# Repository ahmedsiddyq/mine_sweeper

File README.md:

# Mine Sweeper

A software implementation of the classic Minesweeper game.

## Features
- Mine-field generation
- Cell revealing and flagging
- Game-state handling
- Win/loss detection

## Purpose
A practical programming project focused on algorithms, game logic, data structures, and user interaction.

## Author
**Ahmed Siddyq**

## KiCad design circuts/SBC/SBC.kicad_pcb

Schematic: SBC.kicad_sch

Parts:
C1, C5, C10, C13, C14, C15, C16, C46, C51, C52, C53, C55, C56, C58, C63, C64, C65, C80, C95: 2uf; C_0805_2012Metric_Pad1.18x1.45mm_HandSolder
C2, C4, C11, C18, C22, C26, C36, C41, C42, C43, C44, C45, C47, C78, C87: 1nf; C_0201_0603Metric_Pad0.64x0.40mm_HandSolder
C3, C7, C9, C17, C48, C49, C50, C66, C67, C68, C69, C70, C71, C72, C79, C90, C98, C101, C104, C105: 100nf; C_0805_2012Metric_Pad1.18x1.45mm_HandSolder
C6, C19, C23, C27, C37, C54, C57, C60, C88, C96, C97: 470uf; CP_Radial_D8.0mm_P5.00mm
C8: 2pf; C_0805_2012Metric_Pad1.18x1.45mm_HandSolder
C12, C91: 33uf; CP_Radial_D4.0mm_P1.50mm
C20, C21, C28, C29, C34, C38, C39, C40, C82, C89, C99, C100, C102, C103: 2uf; R_0805_2012Metric_Pad1.20x1.40mm_HandSolder
C24, C25, C30, C31, C32, C33, C35, C73, C74, C83, C84, C85, C86, C92, C93: 100nf; R_0805_2012Metric_Pad1.20x1.40mm_HandSolder
C75, C76, C77, C94: C; C_0805_2012Metric_Pad1.18x1.45mm_HandSolder
C81: 470uf; CP_Elec_4x4.5
D1, D4, D5, D10, D12, D13, D14, D43, D44: LED; D_MiniMELF
D2, D3, D6, D7, D46, D47, D48, D49, D54, D55, D56, D57, D58, D59, D60, D61, D62, D63, D64, D65, D66, D67, D68: 1N4004-T_NRND; D_0603_1608Metric_Pad1.05x0.95mm_HandSolder; MPN 1N4004-T; Digi-Key_PN 1N4004DICT-ND
D8, D15, D16, D17, D18, D19: SMAJ6.5A; D_MiniMELF
D11, D21, D24: BZV55B3V3; D_MiniMELF
D20, D25, D26, D45: 1N4004-T_NRND; D_MiniMELF; MPN 1N4004-T; Digi-Key_PN 1N4004DICT-ND
D29, D30, D31, D32, D37, D38, D39, D40, D41, D42: 1N5822; D_MiniMELF
D33, D34, D35, D36: SMAJ26A; D_MiniMELF
D50, D52: L_LED; D_MiniMELF
D51, D53: R_LED; D_MiniMELF
F3, F4: 1A; D_SOD-128
F5, F7: 1A; C_0805_2012Metric_Pad1.18x1.45mm_HandSolder
IC1: PIC16F15243-I_SS; SSOP20_SS_MCH-M; Mouser Part Number 579-PIC16F15243-I/SS
J1: 640456-3; TE_640456-3; MPN 640456-3; Digi-Key_PN A19470-ND
J2: B5B-XH-A_LF__SN_; JST_B5B-XH-A_LF__SN_; MPN B5B-XH-A(LF)(SN); Digi-Key_PN 455-2270-ND
J3: Power; TE_282837-2
J4, J8, J10: DE9_Plug; DB9
J5, J7: OSTTC060162; CONN_6P-OSTTC_OST; MPN OSTTC060162; Digi-Key_PN ED2604-ND
J6: XT60-M; AMASS_XT60-M; PARTREV V1.2
J9: Conn_02x04_Odd_Even; PinHeader_2x04_P2.54mm_Vertical
J11: buzzer; TE_282837-2
J13: Conn_01x04_Pin; PinSocket_1x04_P2.54mm_Vertical
J14: 5v Power; TE_282837-2
J15: Barrel_Jack_MountingPin; BarrelJack_GCT_DCJ200-10-A_Horizontal
Q1, Q2, Q3, Q5, Q6, Q7: MMBTA06; SOT-23
Q4, Q8: IRFS4227; TO-263-3_TabPin2
Q10: BC817; SOT-23
Q11: AO3400A; SOT-23_Handsoldering
R1, R9, R12, R15, R16, R17, R30, R38, R43, R47, R56: 2k; R_0805_2012Metric_Pad1.20x1.40mm_HandSolder
R2, R3, R11, R13, R34, R35, R76, R114, R117, R119: 220; R_0805_2012Metric_Pad1.20x1.40mm_HandSolder
R4, R28, R29, R32, R54, R55, R58: 56k; R_0805_2012Metric_Pad1.20x1.40mm_HandSolder
R5, R6, R14, R36, R37, R60, R61, R62, R63, R120: 5.1k; R_0805_2012Metric_Pad1.20x1.40mm_HandSolder
R7, R21, R50, R51: 470; R_0805_2012Metric_Pad1.20x1.40mm_HandSolder
R8, R24, R25, R39, R52, R53, R64, R65, R66, R67, R68, R69, R70, R71, R80, R90, R91, R92, R93, R94, R95, R96, R97, R98, R107, R121, R122, R123, R124, R125, R126, R127: 10k; R_0805_2012Metric_Pad1.20x1.40mm_HandSolder
R10, R22, R33, R89, R118: 2.2k; R_0805_2012Metric_Pad1.20x1.40mm_HandSolder
R18, R20, R48, R49: 0.3; R_2512_6332Metric_Pad1.40x3.35mm_HandSolder
R19, R23, R46, R77, R112: 330; R_0805_2012Metric_Pad1.20x1.40mm_HandSolder
R26: 26k; R_0805_2012Metric_Pad1.20x1.40mm_HandSolder
R27, R31, R57: 100k; R_0805_2012Metric_Pad1.20x1.40mm_HandSolder
R40, R88, R100, R106: 200; R_0805_2012Metric_Pad1.20x1.40mm_HandSolder
R41, R111, R115, R116: 1.5k; R_0805_2012Metric_Pad1.20x1.40mm_HandSolder
R42: 10; R_0805_2012Metric_Pad1.20x1.40mm_HandSolder
R59, R73: 5k; R_0805_2012Metric_Pad1.20x1.40mm_HandSolder
R72, R74, R75, R84, R85, R86, R87, R109, R110: 1k; R_0805_2012Metric_Pad1.20x1.40mm_HandSolder
R99, R102, R104, R105: 1ohm; R_0805_2012Metric_Pad1.20x1.40mm_HandSolder
R101, R113: 1ohm op*; R_0805_2012Metric_Pad1.20x1.40mm_HandSolder
RV1, RV2: R_Potentiometer; Potentiometer_Bourns_3214W_Vertical
SW1, SW2, SW3, SW4, SW5, SW7: SW_Push; SW_DIP_SPSTx01_Slide_6.7x4.1mm_W6.73mm_P2.54mm_LowProfile_J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
SW6: rst; SW_DIP_SPSTx01_Slide_6.7x4.1mm_W6.73mm_P2.54mm_LowProfile_J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
U1: UC3843; SOIC-8_3.9x4.9mm_P1.27mm
U2, U3, U7, U8: BTS7960B; DPAK127P1490X440-8N; PARTREV 1.1
U4, U9: LM358DT; SOIC-8_3.9x4.9mm_P1.27mm; MPN LM358DT; Digi-Key_PN 497-1591-1-ND
U5: AMS1117-3.3; SOT-223-3_TabPin2
U10: ESP32-DEVKIT-V1; MODULE_ESP32_DEVKIT_V1; PARTREV N/A
U11: PinHeader_1x08_P2.54mm_Vertical
U12, U13: L7805; TO-252-2
U14: L7809; TO-220-3_Vertical
ZD1, ZD8: 3.3v; D_MiniMELF
ZD2, ZD3, ZD4, ZD5, ZD6, ZD7, ZD10, ZD11, ZD12, ZD31, ZD35, ZD36: BZV55B4V7; D_MiniMELF
ZD9: 20v; D_MiniMELF
ZD13, ZD14, ZD15, ZD16, ZD17, ZD18, ZD19, ZD20, ZD21, ZD22, ZD23, ZD24, ZD25, ZD26, ZD27, ZD28, ZD29, ZD30, ZD33, ZD34: 3.3v; D_SOD-123

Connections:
3.3v: C24.1, C35.1, C36.1, C37.1, C38.2, C47.1, C50.1, C53.1, C68.1, D5.2 (A), D6.1 (K), IC1.1 (VDD), J4.4, J8.4, J9.2, J10.4, R64.1, R65.2, R67.1, R69.2, R70.2, R71.2, R76.2, R80.2, R101.1, R105.2, R107.2, R113.1, ZD5.1 (K)
5v block: F7.2, J14.1
5v+: C25.1, C26.1, C27.1, C29.2, C49.1, C52.1, C64.1, C67.1, C76.1, D15.1 (A1), D17.1 (A1), D44.2 (A), D45.2 (A), F4.2, F7.1, J4.3, J5.2, J7.2, J8.3, J10.3, R8.1, R39.1, R40.2, R77.2, R102.1, R104.2, R109.2, R110.2, RV1.3, RV2.3, U10.30 (VIN), ZD7.1 (K), ZD10.1 (K), ZD11.1 (K)
9v+: C82.2, C85.1, C87.1, C88.1, C89.2, D2.2 (A), D43.2 (A), R15.1, R47.1, R99.2, U4.8 (VCC+), U9.8 (VCC+), ZD6.1 (K)
SDA: IC1.9 (RC7)
A1: IC1.5 (RC5), R61.1, ZD20.1 (K)
A2: IC1.7 (RC3), R63.1, ZD22.1 (K)
B1: IC1.2 (RA5), R60.2, ZD19.1 (K)
B2: IC1.8 (RC6), R62.2, ZD21.1 (K)
CS: D3.1 (K), D7.1 (K), U1.3 (CS)
Current_limt1: C83.1, U9.5
Current_limt2: C7.1, R22.1, U4.5
Data_ready: U10.15 (D23), U11.8 (DRDY)
FRQ: D21.1 (K), J13.3, U10.28 (D13)
FSYC: U10.9 (D18), U11.6 (FSSYNC)
GND: C1.2, C2.2, C6.2, C7.2, C8.2, C10.2, C14.2, C15.2, C16.1, C17.2, C18.2, C19.2, C20.1, C22.2, C23.2, C24.2, C25.2, C26.2, C27.2, C28.2, C29.1, C30.1, C31.1, C32.1, C33.1, C34.2, C35.2, C36.2, C37.2, C38.1, C40.2, C41.2, C42.2, C43.2, C44.2, C45.2, C47.2, C48.2, C49.2, C50.2, C51.2, C52.2, C53.2, C54.2, C57.2, C60.2, C63.2, C64.2, C65.1, C66.2, C67.2, C68.2, C69.2, C70.2, C71.2, C72.2, C73.1, C74.1, C75.2, C76.2, C78.2, C79.2, C80.2, C81.2, C82.1, C83.2, C84.1, C85.2, C86.1, C87.2, C88.2, C89.1, C90.2, C92.2, C93.2, C95.1, D8.2 (A2), D11.2 (A), D12.1 (K), D13.1 (K), D14.1 (K), D15.2 (A2), D16.2 (A2), D17.2 (A2), D18.2 (A2), D21.2 (A), D24.2 (A), D30.2 (A), D31.2 (A), D37.2 (A), D39.2 (A), IC1.20 (VSS), J2.3, J3.2, J4.1, J4.5, J4.G1, J4.G2, J5.1, J6.N (NEG), J7.1, J8.1, J8.5, J8.G1, J8.G2, J9.1, J10.1, J10.5, J10.G1, J10.G2, J13.1, J14.2, J15.2, J15.MP (MountPin), Q1.2 (E), Q2.2 (E), Q5.2 (E), Q6.2 (E), Q10.2 (E), Q11.2 (S), R5.2, R6.2, R11.2, R12.2, R14.2, R18.2, R19.2, R20.2, R21.2, R25.2, R26.2, R28.2, R30.2, R32.2, R36.2, R37.2, R41.2, R43.2, R46.2, R48.2, R49.2, R50.2, R53.2, R54.2, R56.2, R58.2, R90.1, R111.2, R112.2, R120.2, R121.1, R122.2, R123.2, R124.2, R125.1, R126.1, R127.2, RV1.1, RV2.1, SW1.2, SW2.2, SW3.2, SW4.2, SW6.2, U1.2 (FB), U1.5 (GND), U4.4 (VCC-), U5.1 (GND), U9.4 (VCC-), U10.2 (GND), U10.29 (GND), U11.3 (GND), U12.2 (GND), U13.2 (GND), U14.2 (GND), ZD1.2 (A), ZD2.2 (A), ZD3.2 (A), ZD4.2 (A), ZD5.2 (A), ZD6.2 (A), ZD7.2 (A), ZD9.2 (A), ZD10.2 (A), ZD11.2 (A), ZD13.2 (A), ZD14.2 (A), ZD15.2 (A), ZD16.2 (A), ZD17.2 (A), ZD18.2 (A), ZD19.2 (A), ZD20.2 (A), ZD21.2 (A), ZD22.2 (A), ZD23.2 (A), ZD24.2 (A), ZD25.2 (A), ZD26.2 (A), ZD27.2 (A), ZD28.2 (A), ZD29.2 (A), ZD30.2 (A), ZD31.2 (A), ZD33.2 (A), ZD34.2 (A), ZD35.2 (A), ZD36.2 (A)
HV: C6.1, C16.2, C17.1, C18.1, C19.1, C20.2, C23.1, C45.1, C48.1, C51.1, C54.1, C57.1, C60.1, C63.1, C66.1, C75.1, C96.1, C97.1, C98.1, C99.2, C100.2, C101.1, C102.2, C103.2, C104.1, C105.1, D4.2 (A), D8.1 (A1), D18.1 (A1), D20.2 (A), D26.1 (K), D29.1 (K), D32.1 (K), D38.1 (K), D40.1 (K), D66.2 (A), D67.2 (A), D68.2 (A), F3.2, J3.1, J4.2, J4.6, J6.P (POS), J8.2, J8.6, J10.2, J10.6, J15.1, R75.2, R88.2, R117.1, U2.7 (VS), U3.7 (VS), U7.7 (VS), U8.7 (VS), ZD12.1 (K), ZD35.1 (K)
INH1: D61.2 (A), D63.2 (A), Q6.3 (C), R38.2
INH2: D59.2 (A), D65.2 (A), Q2.3 (C), R7.2
IRQ: U10.25 (D27)
M1_D1: D62.2 (A), Q5.3 (C), R39.2
M1_L: C9.1, C11.1, C12.2, C13.2, C46.2, C55.2, D31.1 (K), D32.2 (A), D33.2 (A2), D50.2 (A), D51.1 (K), J5.5, U8.4 (OUT), U8.8 (OUT); also elsewhere on the board
M1_R: C9.2, C11.2, C12.1, C13.1, C46.1, C55.1, D29.2 (A), D30.1 (K), D34.2 (A2), J5.6, R115.2, U7.4 (OUT), U7.8 (OUT); also elsewhere on the board
M1_S1: D55.2 (A), D60.2 (A), IC1.16 (RC0)
M1_current_sen: C15.1, IC1.17 (RA2), R59.1, ZD3.1 (K)
M2_D1: D58.2 (A), Q1.3 (C), R8.2
M2_L: C3.1, C4.1, C5.2, C56.2, C58.2, C91.2, D35.2 (A2), D39.1 (K), D40.2 (A), D52.2 (A), D53.1 (K), J7.5, U3.4 (OUT), U3.8 (OUT)
M2_R: C3.2, C4.2, C5.1, C56.1, C58.1, C91.1, D36.2 (A2), D37.1 (K), D38.2 (A), J7.6, R116.2, U2.4 (OUT), U2.8 (OUT)
M2_S1: D56.2 (A), D64.2 (A), IC1.13 (RB4)
M2_current_sen: C10.1, IC1.6 (RC4), R33.1, ZD2.1 (K)
Mcler: C90.1, IC1.4 (~MCLR/VPP/RA3), J2.1, J4.7, J8.7, J10.7, R107.1, SW6.1, U10.26 (D14)
Motor1_OFF: D57.2 (A), IC1.14 (RC2)
Motor2_OFF: D1.2 (A), D54.2 (A), IC1.11 (RB6)
unnamed: C2.1, J1.1, R4.1
unnamed: C21.1, R24.2, R28.1, U4.3
unnamed: C21.2, R25.1, R29.2, U4.2
unnamed: C39.1, R52.2, R54.1, U9.3
unnamed: C39.2, R53.1, R55.2, U9.2
unnamed: C41.1, J5.3, R60.1, R64.2
unnamed: C42.1, J5.4, R61.2, R67.2
unnamed: C43.1, J7.3, R62.1, R66.2
unnamed: C44.1, J7.4, R63.2, R68.2
unnamed: C92.1, R89.1, U9.6
unnamed: C93.1, RV1.2, U4.6
unnamed: D1.1 (K), R19.1
unnamed: D2.1 (K), R106.2
unnamed: C28.1, D3.2 (A), R31.1, R32.1
unnamed: D4.1 (K), R41.1
unnamed: D5.1 (K), R46.1
unnamed: D6.2 (A), J2.2
unnamed: C40.1, D7.2 (A), R57.1, R58.1
unnamed: D10.2 (A), R72.2
unnamed: D12.2 (A), R75.1
unnamed: D13.2 (A), R77.1
unnamed: D14.2 (A), R76.1
unnamed: C78.1, C79.1, C80.1, C81.1, D16.1 (A1), R113.2, U10.1 (3V3)
unnamed: C33.2, D25.2 (A), U14.3 (OUT)
unnamed: D25.1 (K), R99.1
unnamed: D26.2 (A), F3.1
unnamed: D33.1 (A1), D34.1 (A1)
unnamed: D35.1 (A1), D36.1 (A1)
unnamed: C34.1, D41.2 (A), Q7.2 (E), Q8.3 (S), R48.1, R49.1, R52.1
unnamed: C97.2, C98.2, C99.1, C103.1, C105.2, D41.1 (K), Q8.2 (D), U7.1 (GND), U8.1 (GND)
unnamed: C14.1, D42.2 (A), Q3.2 (E), Q4.3 (S), R18.1, R20.1, R24.1
unnamed: C96.2, C100.1, C101.2, C102.1, C104.2, D42.1 (K), Q4.2 (D), U2.1 (GND), U3.1 (GND)
unnamed: D43.1 (K), R111.1
unnamed: D44.1 (K), R112.1
unnamed: D45.1 (K), R114.2
unnamed: D46.1 (K), R13.1
unnamed: D47.1 (K), Q3.1 (B), R13.2, R14.1
unnamed: D48.1 (K), R119.1
unnamed: D49.1 (K), Q7.1 (B), R119.2, R120.1
unnamed: D50.1 (K), D51.2 (A), R115.1
unnamed: D52.1 (K), D53.2 (A), R116.1
unnamed: D54.1 (K), R2.1, ZD13.1 (K)
unnamed: D55.1 (K), R34.1, ZD15.1 (K)
unnamed: D56.1 (K), R3.1, ZD14.1 (K)
unnamed: D57.1 (K), R35.1, ZD16.1 (K)
unnamed: D58.1 (K), R92.1
unnamed: D59.1 (K), R91.1
unnamed: D60.1 (K), R96.2
unnamed: D61.1 (K), R95.2
unnamed: D62.1 (K), R98.1
unnamed: D63.1 (K), R97.1
unnamed: D64.1 (K), R94.2
unnamed: D65.1 (K), R93.2
unnamed: D66.1 (K), R27.1
unnamed: D67.1 (K), R100.2, ZD8.1 (K)
unnamed: D68.1 (K), U1.7 (VCC)
unnamed: IC1.12 (RB5), R17.1
unnamed: IC1.15 (RC1), R16.1
unnamed: J1.3, R1.2
unnamed: F5.2, J11.1
unnamed: J13.4, R117.2
unnamed: Q1.1 (B), R3.2, R6.1
unnamed: Q2.1 (B), R2.2, R5.1
unnamed: Q3.3 (C), Q4.1 (G), R15.2
unnamed: Q5.1 (B), R34.2, R36.1
unnamed: Q6.1 (B), R35.2, R37.1
unnamed: Q7.3 (C), Q8.1 (G), R47.2
unnamed: Q10.1 (B), R74.2
unnamed: Q10.3 (C), Q11.1 (G), R73.2
unnamed: R22.2, R29.1, R31.2, R33.2, U4.1
unnamed: R51.2, U4.7
unnamed: R55.1, R57.2, R59.2, U9.1
unnamed: R66.1, R68.1
unnamed: R84.1, SW1.1
unnamed: R85.1, SW2.1
unnamed: R86.1, SW3.1
unnamed: R87.1, SW4.1
unnamed: R89.2, RV2.2
unnamed: R109.1, SW7.2
unnamed: R110.1, SW5.2
unnamed: R118.2, U9.7
unnamed: R9.2, U1.1 (COMP)
unnamed: R10.1, U1.6 (OUT)
unnamed: J1.2, U1.4 (RC)
unnamed: R92.2, R121.2, U2.2 (IN), ZD24.1 (K)
unnamed: R12.1, U2.5 (SR)
unnamed: R94.1, R123.1, U3.2 (IN), ZD25.1 (K)
unnamed: R30.1, U3.5 (SR)
unnamed: C30.2, R40.1, U5.3 (VI)
unnamed: C32.2, R105.1, U5.2 (VO)
unnamed: R98.2, R124.1, U7.2 (IN), ZD28.1 (K)
unnamed: R43.1, U7.5 (SR)
unnamed: R96.1, R127.1, U8.2 (IN), ZD29.1 (K)
unnamed: R56.1, U8.5 (SR)
unnamed: C65.2, R101.2, U11.2 (3.3V)
unnamed: C95.2, R102.2, U11.1 (VCC)
unnamed: C84.2, R106.1, U12.1 (IN)
unnamed: C86.2, R104.1, U12.3 (OUT)
unnamed: C73.2, R88.1, U13.1 (IN), ZD12.2 (A)
unnamed: C74.2, F4.1, U13.3 (OUT)
unnamed: C31.2, R42.1, U14.1 (IN), ZD9.1 (K)
unnamed: C22.1, R23.2, R26.1, R27.2, ZD4.1 (K)
unnamed: R42.2, R100.1, ZD8.2 (A)
PGC: IC1.18 (RA1/ICSPCLK), J2.5, R1.1
PGD: D46.2 (A), D48.2 (A), IC1.19 (RA0/ICSPDAT), J2.4
PWM: C8.1, R7.1, R10.2, R11.1, R38.1, ZD1.1 (K)
SCL: IC1.10 (RB7), J4.8, J8.8, J10.8, R65.1, R70.1, U10.14 (D22), ZD18.1 (K), ZD33.1 (K), ZD36.1 (K)
SCL2: U10.6 (RX2), U11.4 (SCL)
SDA: J4.9, J8.9, J10.9, R69.1, R71.1, U10.11 (D21), ZD17.1 (K), ZD31.1 (K), ZD34.1 (K)
SDA2: U10.7 (TX2), U11.5 (SDA)
SW1: C69.1, R80.1, R84.2, U10.21 (D32)
SW2: C71.1, R86.2, U10.22 (D33)
SW3: C72.1, R87.2, U10.20 (D35)
SW4: C70.1, R85.2, U10.19 (D34)
buzz: D11.1 (K), R74.1, U10.5 (D4)
buzzing_gnd: C77.2, C94.2, D10.1 (K), D19.2 (A2), J11.2, Q11.3 (D)
buzzing_vcc: C77.1, C94.1, D19.1 (A1), D20.1 (K), F5.1, R72.1, R73.1, R114.1
care0: U10.12 (RX0), U10.13 (TX0)
carei: U10.4 (D2)
carett: U10.3 (D15)
careuu: U10.27 (D12)
detect: D24.1 (K), J13.2, U10.8 (D5)
error 1: R16.2, R50.1, U7.6 (IS), U8.6 (IS)
error 2: R17.2, R21.1, U2.6 (IS), U3.6 (IS)
int_a: U10.10 (D19), U11.7 (INTA)
kill1: D49.2 (A), R118.1
kill2: D47.2 (A), R51.1
s5v+: C1.1, R4.2, R9.1, U1.8 (VREF)
tst1: R95.1, R97.2, R125.2, R126.2, SW5.1, U7.3 (INH), U8.3 (INH), ZD27.1 (K), ZD30.1 (K)
tst2: R90.2, R91.2, R93.1, R122.1, SW7.1, U2.3 (INH), U3.3 (INH), ZD23.1 (K), ZD26.1 (K)
voltge_sen: IC1.3 (RA4), R23.1

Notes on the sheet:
speed_con
dir_con

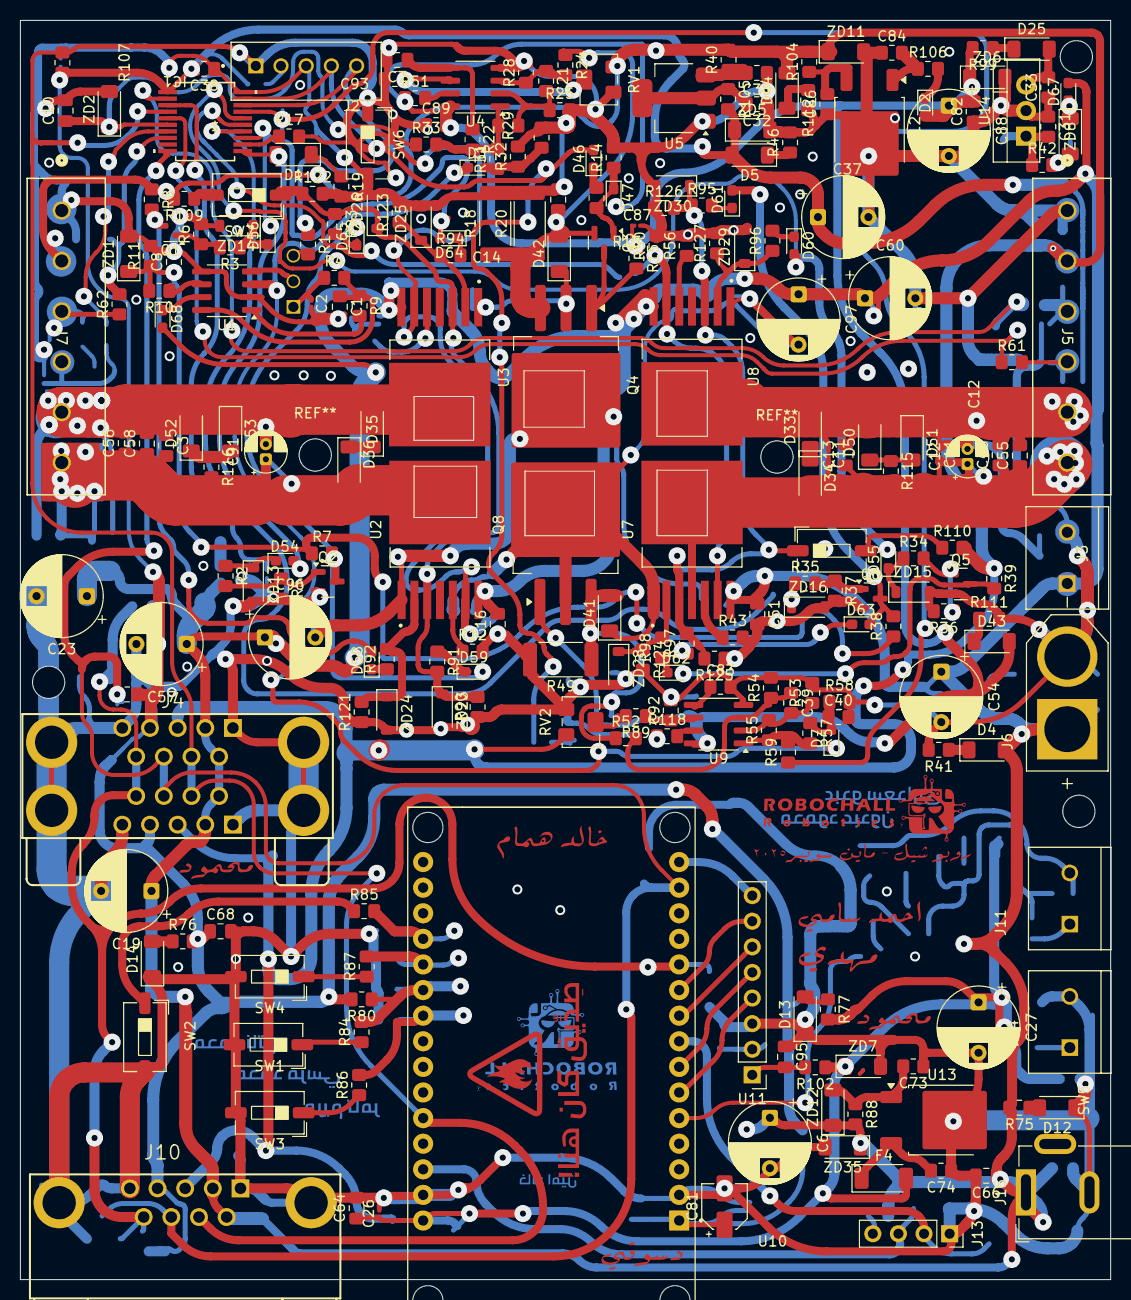
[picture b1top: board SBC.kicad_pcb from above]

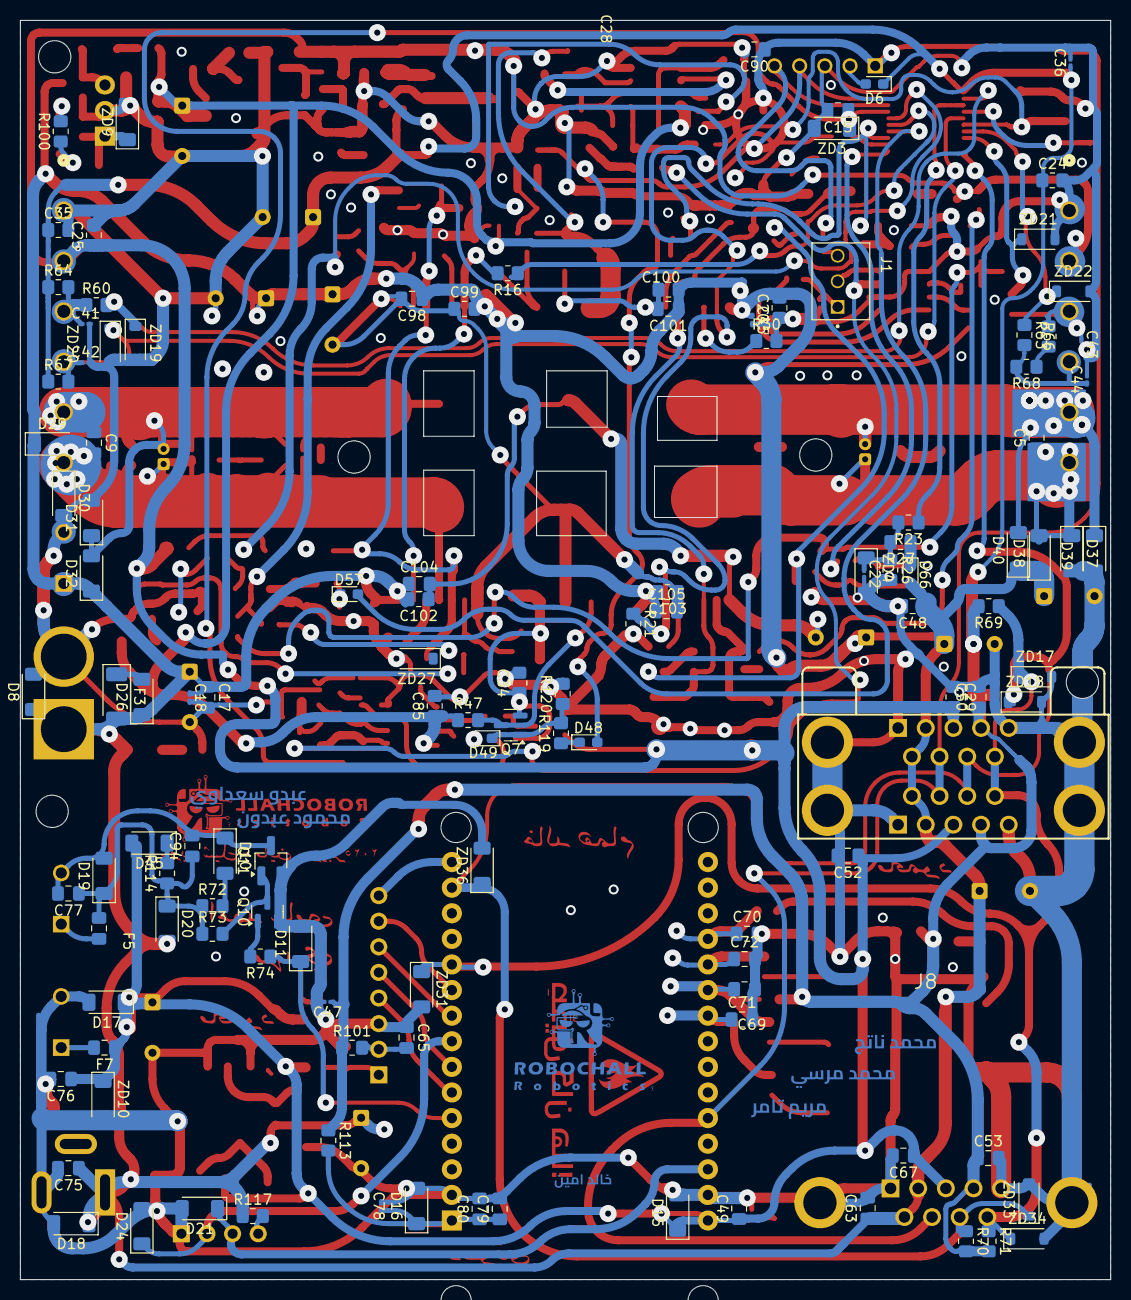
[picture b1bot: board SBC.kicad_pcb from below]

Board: 2 copper layers, 108.2 x 124.9 mm, 367 parts (123 on the bottom side), 159 nets.

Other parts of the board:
C11#2: 1nf; C_0201_0603Metric_Pad0.64x0.40mm_HandSolder

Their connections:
M1_L: C11#2.1; also elsewhere on the board
M1_R: C11#2.2; also elsewhere on the board

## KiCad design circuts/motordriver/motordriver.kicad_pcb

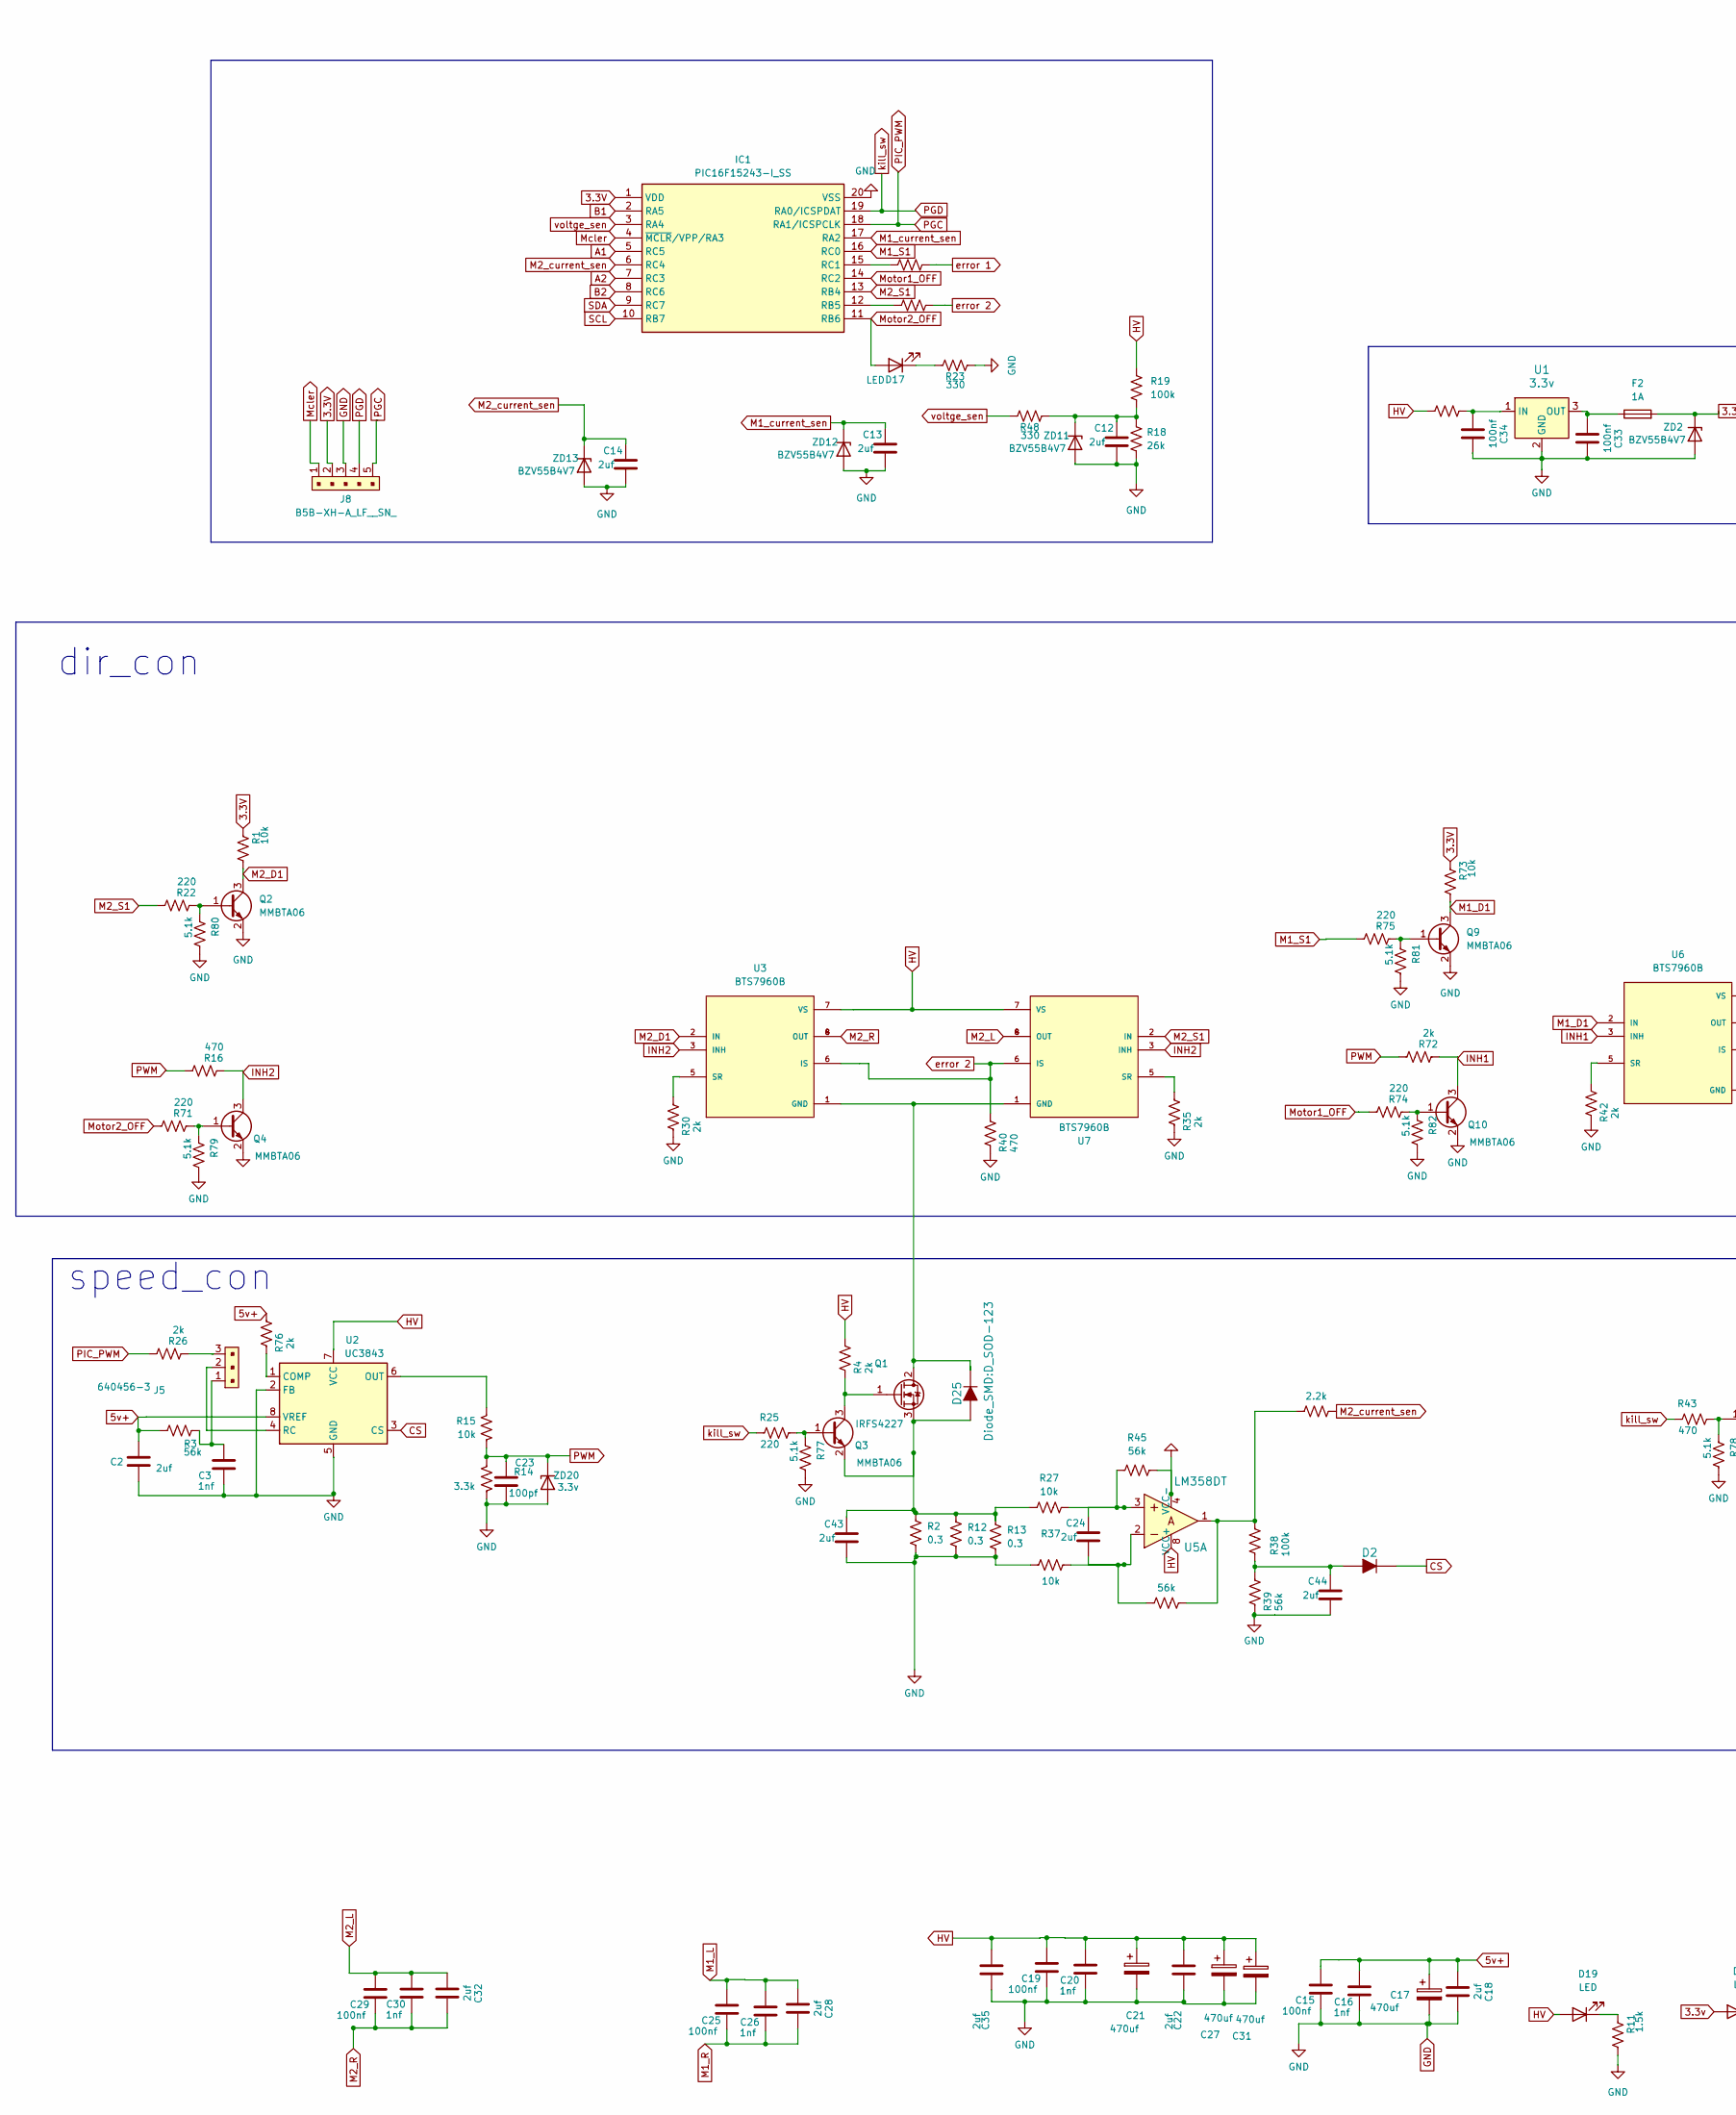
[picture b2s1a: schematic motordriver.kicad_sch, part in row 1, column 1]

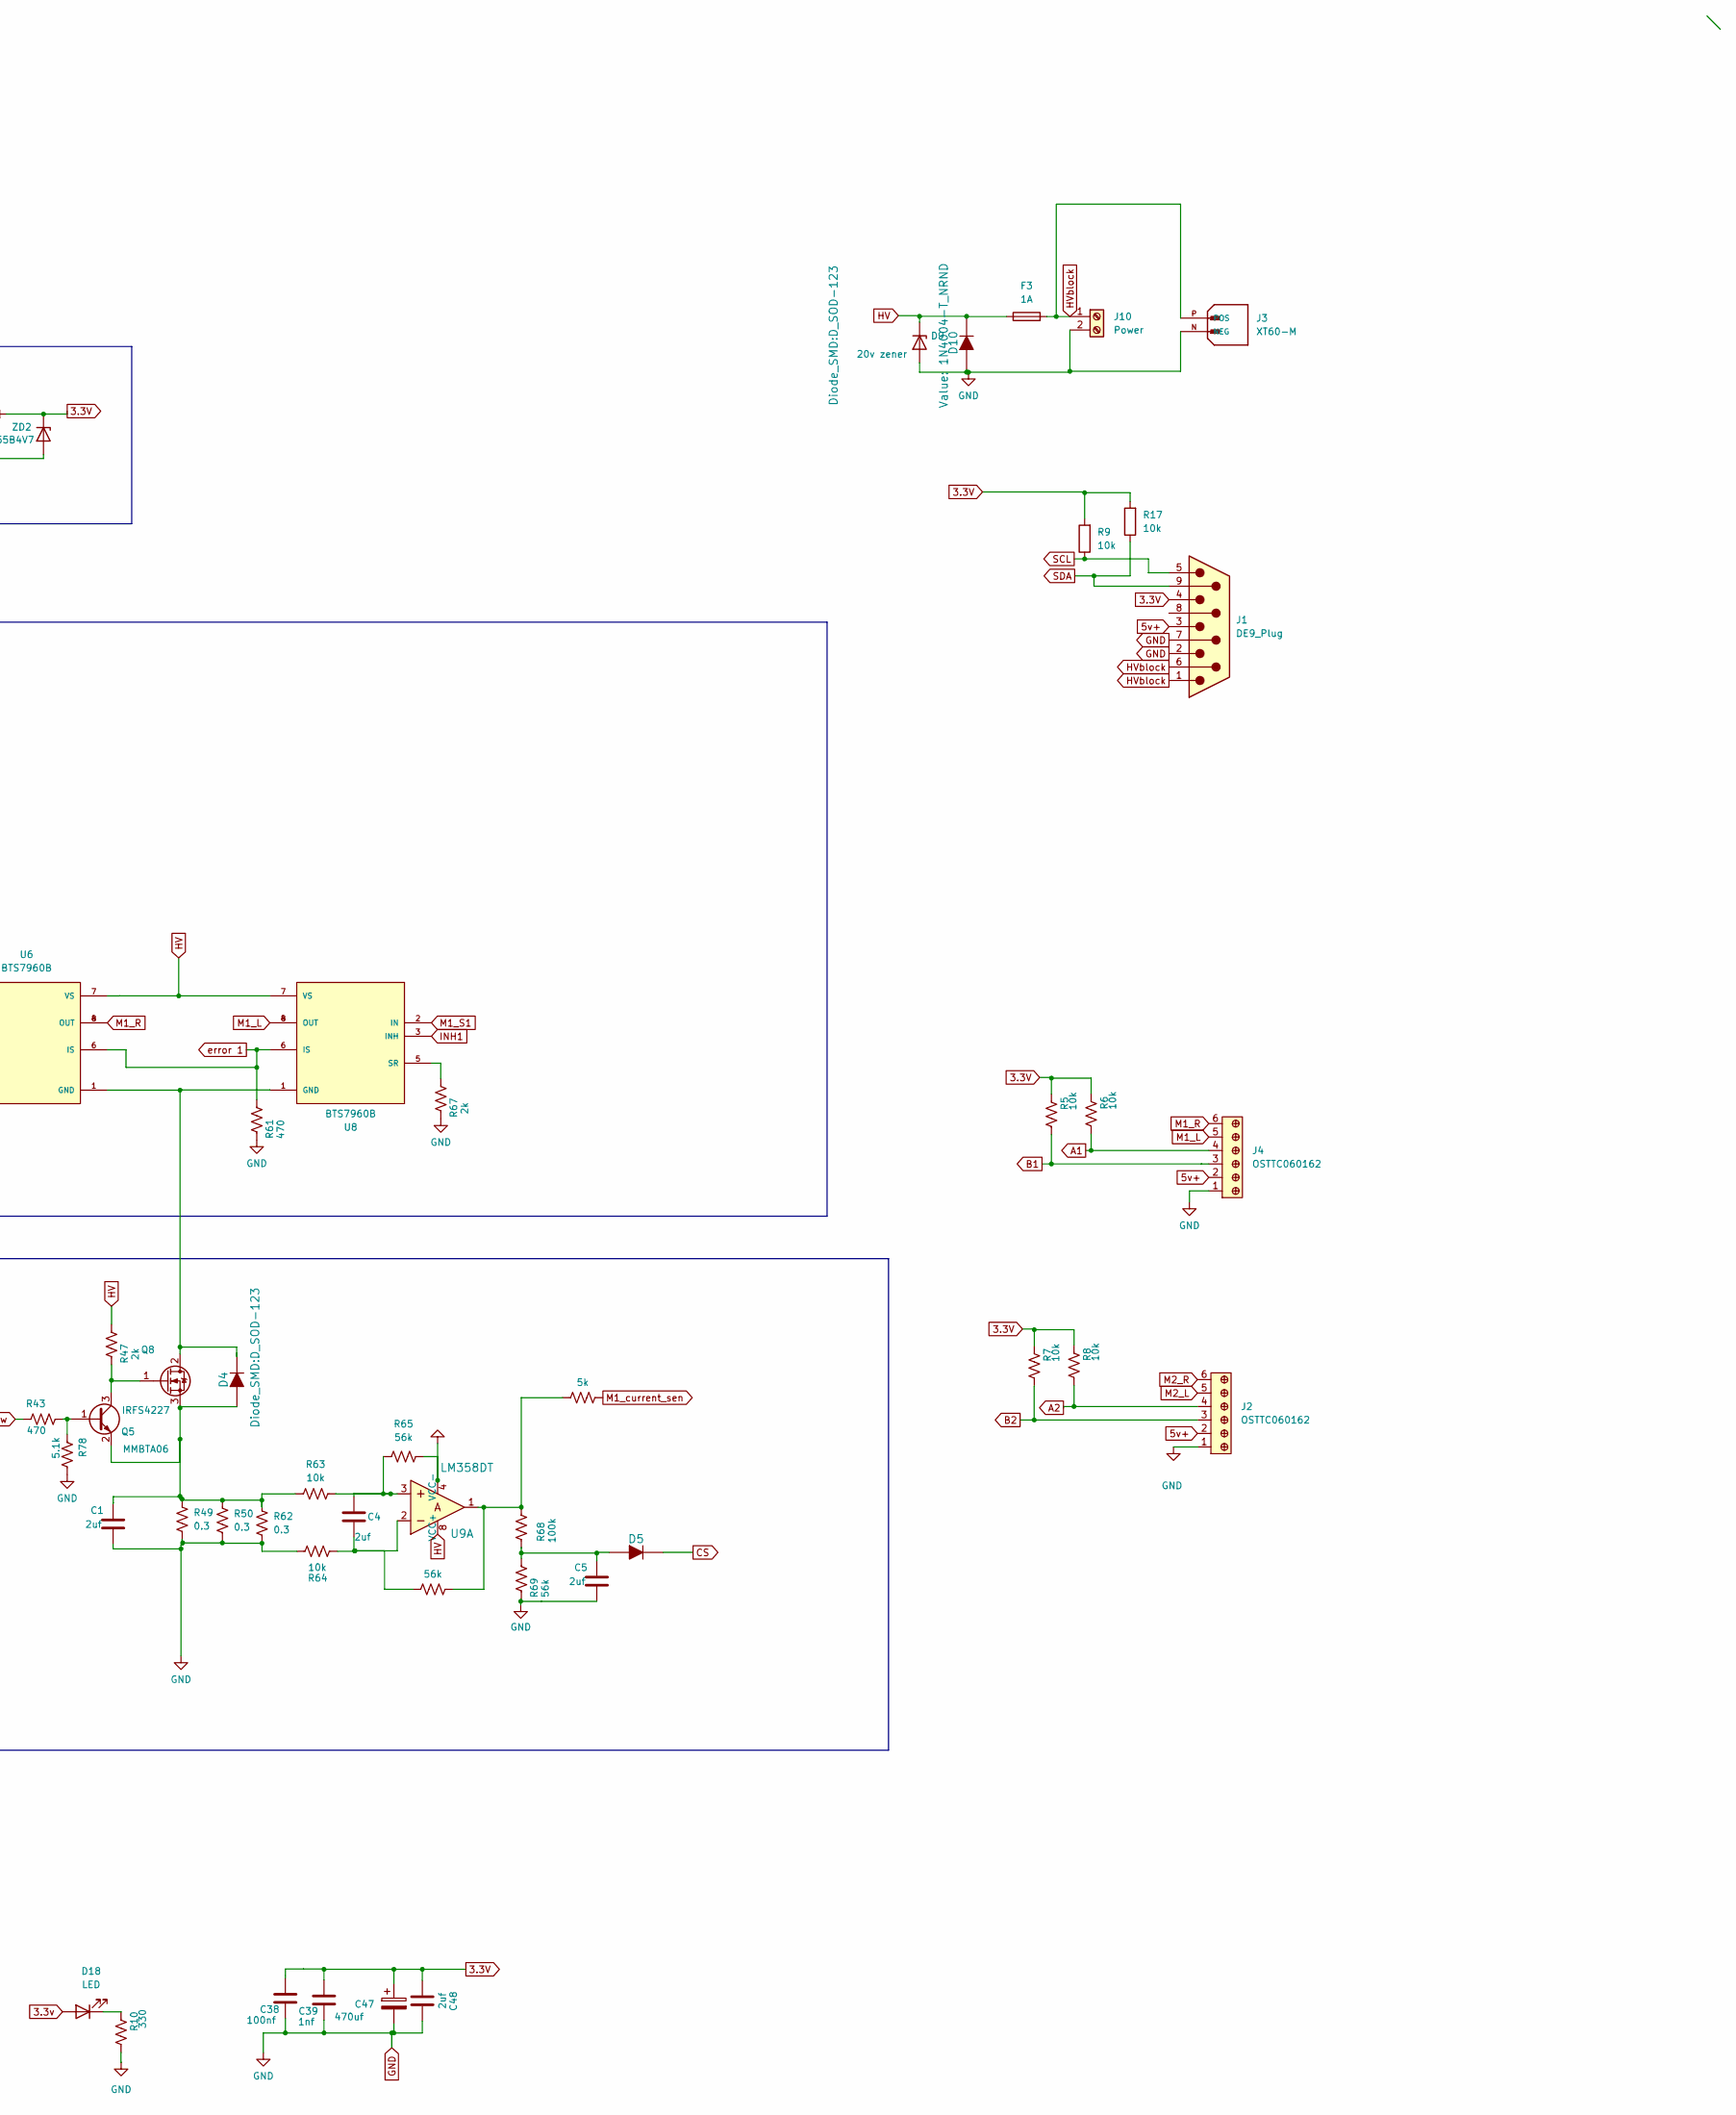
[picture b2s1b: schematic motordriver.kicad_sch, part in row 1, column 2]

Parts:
C1, C2, C4, C5, C13, C14, C18, C22, C24, C28, C32, C35, C43, C44, C48: 2uf; R_0805_2012Metric_Pad1.20x1.40mm_HandSolder
C3, C16, C20, C26, C30, C39: 1nf; R_0805_2012Metric_Pad1.20x1.40mm_HandSolder
C12: 2uf; CP_Radial_D8.0mm_P5.00mm
C15, C19, C25, C29, C33, C34, C38: 100nf; R_0805_2012Metric_Pad1.20x1.40mm_HandSolder
C17, C21, C27, C31, C47: 470uf; CP_Radial_D8.0mm_P5.00mm
C23: 100pf; R_0805_2012Metric_Pad1.20x1.40mm_HandSolder
D2, D4, D5, D10, D25: 1N4004-T_NRND; D_SOD-123; MPN 1N4004-T; Digi-Key_PN 1N4004DICT-ND
D9: 20v zener; D_MiniMELF
D17, D18, D19: LED; D_SOD-123
F2, F3: 1A; D_SOD-128
IC1: PIC16F15243-I_SS; SSOP20_SS_MCH-M; Mouser Part Number 579-PIC16F15243-I/SS
J1: DE9_Plug; DB9
J2, J4: OSTTC060162; CONN_6P-OSTTC_OST; MPN OSTTC060162; Digi-Key_PN ED2604-ND
J3: XT60-M; AMASS_XT60-M; PARTREV V1.2
J5: 640456-3; TE_640456-3; MPN 640456-3; Digi-Key_PN A19470-ND
J8: B5B-XH-A_LF__SN_; JST_B5B-XH-A_LF__SN_; MPN B5B-XH-A(LF)(SN); Digi-Key_PN 455-2270-ND
J10: Power; TE_282837-2
Q1, Q8: IRFS4227; TO-263-3_TabPin2
Q2, Q3, Q4, Q5, Q9, Q10: MMBTA06; SOT-23
R1, R5, R6, R7, R8, R9, R15, R17, R27, R37, R63, R64, R73: 10k; R_0805_2012Metric_Pad1.20x1.40mm_HandSolder
R2, R12, R13, R49, R50, R62: 0.3; R_Axial_DIN0414_L11.9mm_D4.5mm_P25.40mm_Horizontal
R3, R39, R44, R45, R65, R66, R69: 56k; R_0805_2012Metric_Pad1.20x1.40mm_HandSolder
R4, R26, R30, R35, R36, R41, R42, R47, R67, R72, R76: 2k; R_0805_2012Metric_Pad1.20x1.40mm_HandSolder
R10, R23, R48: 330; R_0805_2012Metric_Pad1.20x1.40mm_HandSolder
R11: 1.5k; R_0805_2012Metric_Pad1.20x1.40mm_HandSolder
R14: 3.3k; R_0805_2012Metric_Pad1.20x1.40mm_HandSolder
R16, R40, R43, R61: 470; R_0805_2012Metric_Pad1.20x1.40mm_HandSolder
R18: 26k; R_0805_2012Metric_Pad1.20x1.40mm_HandSolder
R19, R38, R68: 100k; R_0805_2012Metric_Pad1.20x1.40mm_HandSolder
R20: 200; R_Bare_Metal_Element_L16.3mm_W4.8mm_P15.30mm
R22, R25, R71, R74, R75: 220; R_0805_2012Metric_Pad1.20x1.40mm_HandSolder
R46: 2.2k; R_0805_2012Metric_Pad1.20x1.40mm_HandSolder
R70: 5k; R_0805_2012Metric_Pad1.20x1.40mm_HandSolder
R77, R78, R79, R80, R81, R82: 5.1k; R_0805_2012Metric_Pad1.20x1.40mm_HandSolder
U1: 3.3v; SOT230P700X180-4N; MPN LM7805CT; Digi-Key_PN LM7805CT-ND
U2: UC3843; SOIC-8_3.9x4.9mm_P1.27mm
U3, U6, U7, U8: BTS7960B; DPAK127P1490X440-8N; PARTREV 1.1
U5, U9: LM358DT; SOIC-8_3.9x4.9mm_P1.27mm; MPN LM358DT; Digi-Key_PN 497-1591-1-ND
ZD2, ZD12, ZD13: BZV55B4V7; D_MiniMELF
ZD11: BZV55B4V7; CP_Radial_D10.0mm_P5.00mm_P7.50mm
ZD20: 3.3v; D_MiniMELF

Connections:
3.3V: C38.1, C39.1, C47.1, C48.2, F2.2, IC1.1 (VDD), J1.4, J8.2, R1.1, R5.1, R6.1, R7.1, R8.1, R9.2, R17.2, R73.1, ZD2.1 (K)
3.3v: D18.2 (A)
5v+: C2.1, C15.1, C16.1, C17.1, C18.2, J1.3, J2.2, J4.2, R3.2, R76.1, U2.8 (VREF)
SDA: IC1.9 (RC7)
A1: IC1.5 (RC5), J4.4, R6.2
A2: IC1.7 (RC3), J2.4, R8.2
B1: IC1.2 (RA5), J4.3, R5.2
B2: IC1.8 (RC6), J2.3, R7.2
CS: D2.1 (K), D5.1 (K), U2.3 (CS)
GND: C1.2, C2.2, C3.2, C5.2, C12.2, C13.2, C14.2, C15.2, C16.2, C17.2, C18.1, C19.2, C20.2, C21.2, C22.1, C23.2, C27.2, C31.2, C33.1, C34.1, C35.1, C38.2, C39.2, C43.2, C44.2, C47.2, C48.1, D9.2 (A), D10.2 (A), IC1.20 (VSS), J1.2, J1.7, J2.1, J3.N (NEG), J4.1, J8.3, J10.2, Q2.2 (E), Q4.2 (E), Q9.2 (E), Q10.2 (E), R2.2, R10.2, R11.2, R12.2, R13.2, R14.2, R18.2, R23.2, R30.2, R35.2, R37.2, R39.2, R40.2, R42.2, R45.2, R49.2, R50.2, R61.2, R62.2, R64.2, R65.2, R67.2, R69.2, R77.2, R78.2, R79.2, R80.2, R81.2, R82.2, U1.2 (GND), U2.2 (FB), U2.5 (GND), U5.4 (VCC-), U9.4 (VCC-), ZD2.2 (A), ZD11.2 (A), ZD12.2 (A), ZD13.2 (A), ZD20.2 (A)
HV: C19.1, C20.1, C21.1, C22.2, C27.1, C31.1, C35.2, D9.1 (K), D10.1 (K), D19.2 (A), F3.1, R4.1, R19.1, R20.2, R47.1, U2.7 (VCC), U3.7 (VS), U5.8 (VCC+), U6.7 (VS), U7.7 (VS), U8.7 (VS), U9.8 (VCC+)
HVblock: F3.2, J1.1, J1.6, J3.P (POS), J10.1
INH1: Q10.3 (C), R72.2, U6.3 (INH), U8.3 (INH)
INH2: Q4.3 (C), R16.2, U3.3 (INH), U7.3 (INH)
M1_D1: Q9.3 (C), R73.2, U6.2 (IN)
M1_L: C25.1, C26.1, C28.2, J4.5, U8.4 (OUT), U8.8 (OUT)
M1_R: C25.2, C26.2, C28.1, J4.6, U6.4 (OUT), U6.8 (OUT)
M1_S1: IC1.16 (RC0), R75.1, U8.2 (IN)
M1_current_sen: C13.1, IC1.17 (RA2), R70.1, ZD12.1 (K)
M2_D1: Q2.3 (C), R1.2, U3.2 (IN)
M2_L: C29.1, C30.1, C32.2, J2.5, U7.4 (OUT), U7.8 (OUT)
M2_R: C29.2, C30.2, C32.1, J2.6, U3.4 (OUT), U3.8 (OUT)
M2_S1: IC1.13 (RB4), R22.1, U7.2 (IN)
M2_current_sen: C14.1, IC1.6 (RC4), R46.1, ZD13.1 (K)
Mcler: IC1.4 (~MCLR/VPP/RA3), J8.1
Motor1_OFF: IC1.14 (RC2), R74.1
Motor2_OFF: D17.2 (A), IC1.11 (RB6), R71.1
unnamed: C3.1, J5.1, R3.1
unnamed: C4.1, R63.2, R65.1, U9.3
unnamed: C4.2, R64.1, R66.2, U9.2
unnamed: C24.1, R27.2, R45.1, U5.3
unnamed: C24.2, R37.1, R44.2, U5.2
unnamed: C44.1, D2.2 (A), R38.1, R39.1
unnamed: C1.1, D4.2 (A), Q5.2 (E), Q8.3 (S), R49.1, R50.1, R62.1, R63.1
unnamed: D4.1 (K), Q8.2 (D), U6.1 (GND), U8.1 (GND)
unnamed: C5.1, D5.2 (A), R68.1, R69.1
unnamed: D17.1 (K), R23.1
unnamed: D18.1 (K), R10.1
unnamed: D19.1 (K), R11.1
unnamed: C43.1, D25.2 (A), Q1.3 (S), Q3.2 (E), R2.1, R12.1, R13.1, R27.1
unnamed: D25.1 (K), Q1.2 (D), U3.1 (GND), U7.1 (GND)
unnamed: IC1.12 (RB5), R36.1
unnamed: IC1.15 (RC1), R41.1
unnamed: J5.3, R26.2
unnamed: Q1.1 (G), Q3.3 (C), R4.2
unnamed: Q2.1 (B), R22.2, R80.1
unnamed: Q3.1 (B), R25.2, R77.1
unnamed: Q4.1 (B), R71.2, R79.1
unnamed: Q5.1 (B), R43.2, R78.1
unnamed: Q5.3 (C), Q8.1 (G), R47.2
unnamed: Q9.1 (B), R75.2, R81.1
unnamed: Q10.1 (B), R74.2, R82.1
unnamed: R38.2, R44.1, R46.2, U5.1
unnamed: R66.1, R68.2, R70.2, U9.1
unnamed: C34.2, R20.1, U1.1 (IN)
unnamed: C33.2, F2.1, U1.3 (OUT)
unnamed: R76.2, U2.1 (COMP)
unnamed: R15.1, U2.6 (OUT)
unnamed: J5.2, U2.4 (RC)
unnamed: R30.1, U3.5 (SR)
unnamed: R42.1, U6.5 (SR)
unnamed: R35.1, U7.5 (SR)
unnamed: R67.1, U8.5 (SR)
unnamed: C12.1, R18.1, R19.2, R48.2, ZD11.1 (K)
PGC: IC1.18 (RA1/ICSPCLK), J8.5, R26.1
PGD: IC1.19 (RA0/ICSPDAT), J8.4, R25.1, R43.1
PWM: C23.1, R14.1, R15.2, R16.1, R72.1, ZD20.1 (K)
SCL: IC1.10 (RB7), J1.5, R9.1
SDA: J1.9, R17.1
error 1: R41.2, R61.1, U6.6 (IS), U8.6 (IS)
error 2: R36.2, R40.1, U3.6 (IS), U7.6 (IS)
voltge_sen: IC1.3 (RA4), R48.1

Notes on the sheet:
speed_con
dir_con

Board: 2 copper layers, 141 parts (0 on the bottom side), 70 nets, no tracks yet.

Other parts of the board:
REF1, REF2: MountingHole_3.2mm_M3

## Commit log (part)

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2025-06-04 local_grib
2025-06-07 compact ic int
2025-06-17 last_touches
2025-06-17 last
2025-06-18 lay out
2025-06-19 edited lay out
2025-06-19 heatsink considered
2025-06-21 lasy update smd res
2025-06-26 make the full
2025-06-28 start
2025-06-29 29-6 siddyq
2025-07-01 layout
2025-07-05 siddyq 7-5 finshing befor ly mod
2025-07-06 LAST EDIT AT 7-6
2025-07-08 sidyq 7-8 using curren amp design
2025-07-08 7-8 start layouting
2025-07-08 7-8 AT 2 PM LAYOUT EDITING
2025-07-08 lay-out frist low side
2025-07-09 7-9 siddyq mid layout
2025-07-09 test
2025-07-10 siddyq at 11.26
2025-07-11 almost ready
2025-07-11 bom has been deplated
2025-07-11 bommmb has been depated
2025-07-18 siddyq at fanaly
2025-07-18 BEFOR R MOTER EDIT OP-AMP
2025-07-25 siddyq has done almost done 7-25
2025-07-25 siddyq test plane
2025-07-25 siddyq done
2025-07-25 siddyq has done it
2025-07-26 siddyq has finsh siddyq is done oh this feeling
2025-08-13 sidd [[
2025-08-22 @code
2025-08-30 siddyq @ final weeks edit code with 2 motor about calbrated
